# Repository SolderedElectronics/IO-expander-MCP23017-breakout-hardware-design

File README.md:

# IO expander MCP23017 breakout Hardware Design

## About the Product

|  |
| :----------------------------------------------------------: |
| [Buy IO expander MCP23017 breakout](https://www.solde.red/333007) |

Are you short on IO pins? Looking to increase the number of them? That’s what the GPIO Expander MCP23017 is for! It uses I2C communication to do so. With just two wires, 16 new fully configurable digital IO pins are added to a microcontroller.

Due to the jumpers on the board, the I2C address of a device can be changed. Thus, eight breakout boards can be connected to a microcontroller. All of the pins on the expander board have pull-out resistors that can be turned on and off.

---

## Repository Contents

This repository contains all design files for IO expander MCP23017 breakout, organized as follows:

- **`CAD` folder**: Contains KiCAD design files, including:
  - Schematics
  - PCB layout
  - Panel PCB layout
  - Source 3D files in Fusion360, if any
  - All files are sorted by version with a detailed change log.
- **`OUTPUTS` folder**: Includes all production-ready files, such as:
  - Bill of Materials (BOM) and interactive BOM (iBOM)
  - PDF versions of schematics
  - 3D `.step` file of the board
  - 3D-printable models
  - Gerber files for PCB manufacturing
  - Image of the pinout of the board
  - Product image
  - Compliance, legal and generic sales documents

Refer to the `Change Log` in the CAD folder for details about updates between versions.

---

## Learn More About the Product

Beyond the repository, explore the following resources:

### Soldered Verify

The **Soldered Verify** system ensures every board you purchase from Soldered is fully functional. It also provides access to exclusive test data for your product. To get started, find the unique Soldered Verify ID on your product's packaging and enter the ID on the [Soldered Verify page](https://soldered.com/verify/) to access test results and additional product details.

### Soldered Community

Soldered Community is your go-to place for technical support. Our engineers track and answer all questions posted there, and it’s a great space for the maker community. Get answers to your questions and solutions for your challenges at [Soldered Community](https://soldered.com/community).

### solde.red

solde.red is an ultimate URL shortener and information hub. Access it by typing solde.red/ followed by your product SKU, e.g., [solde.red/333000](https://solde.red/333000), to find getting-started guides, datasheets, open-source hardware and software files, certifications, images, pinouts, and more. Read more about the shortener [here](https://solde.red/info/).

---

## Contributing

Contributions are welcome! Here’s how you can get involved:

- Submit pull requests to enhance the design or fix issues.
- Report bugs or problems by opening an issue.

We encourage community collaboration to make this product even better.

---

## About Soldered

[Soldered for Makers](https://soldered.com) specializes in designing and manufacturing electronic products tailored for enthusiasts, ranging from hobbyists to professionals. Our portfolio includes electronic boards, sensors, and actuators that are widely utilized in fields such as microelectronics, mechatronics, robotics, programming, and IoT. Every product we offer is designed in-house and built upon open-source hardware and software platforms. Proudly certified and manufactured within the European Union, our catalog likely includes the product you need for your project.

We complement these products with comprehensive tutorials and manuals, product descriptions, schematics, programming codes, and project examples. Our round-the-clock [customer and technical support](https://soldered.com/community) is available for all our products, irrespective of the sales channel. Soldered’s success and services reflect our maker community’s unwavering [trust](https://www.trustpilot.com/review/soldered.com), for which we are deeply grateful. Join our community and create using Soldered products.

---

## License

All Soldered open-source hardware (OSH) is under The TAPR Open Hardware License. Read more in the LICENSE file located in this repository.

**Disclaimer:**

No warranty - all designs in this repository are distributed in the hope that they will be useful, but without any warranty. They are provided "AS IS", therefore without warranty of any kind, either expressed or implied. The entire quality and performance of what you do with the contents of this repository are your responsibility. In no event Soldered Electronics will be liable for your damages, or losses, including any general, special, incidental, or consequential damage arising out of the use or inability to use the contents of this repository. 

---

## Have fun!

Thank you for your support from your fellow makers at Soldered Electronics.

Happy Making!

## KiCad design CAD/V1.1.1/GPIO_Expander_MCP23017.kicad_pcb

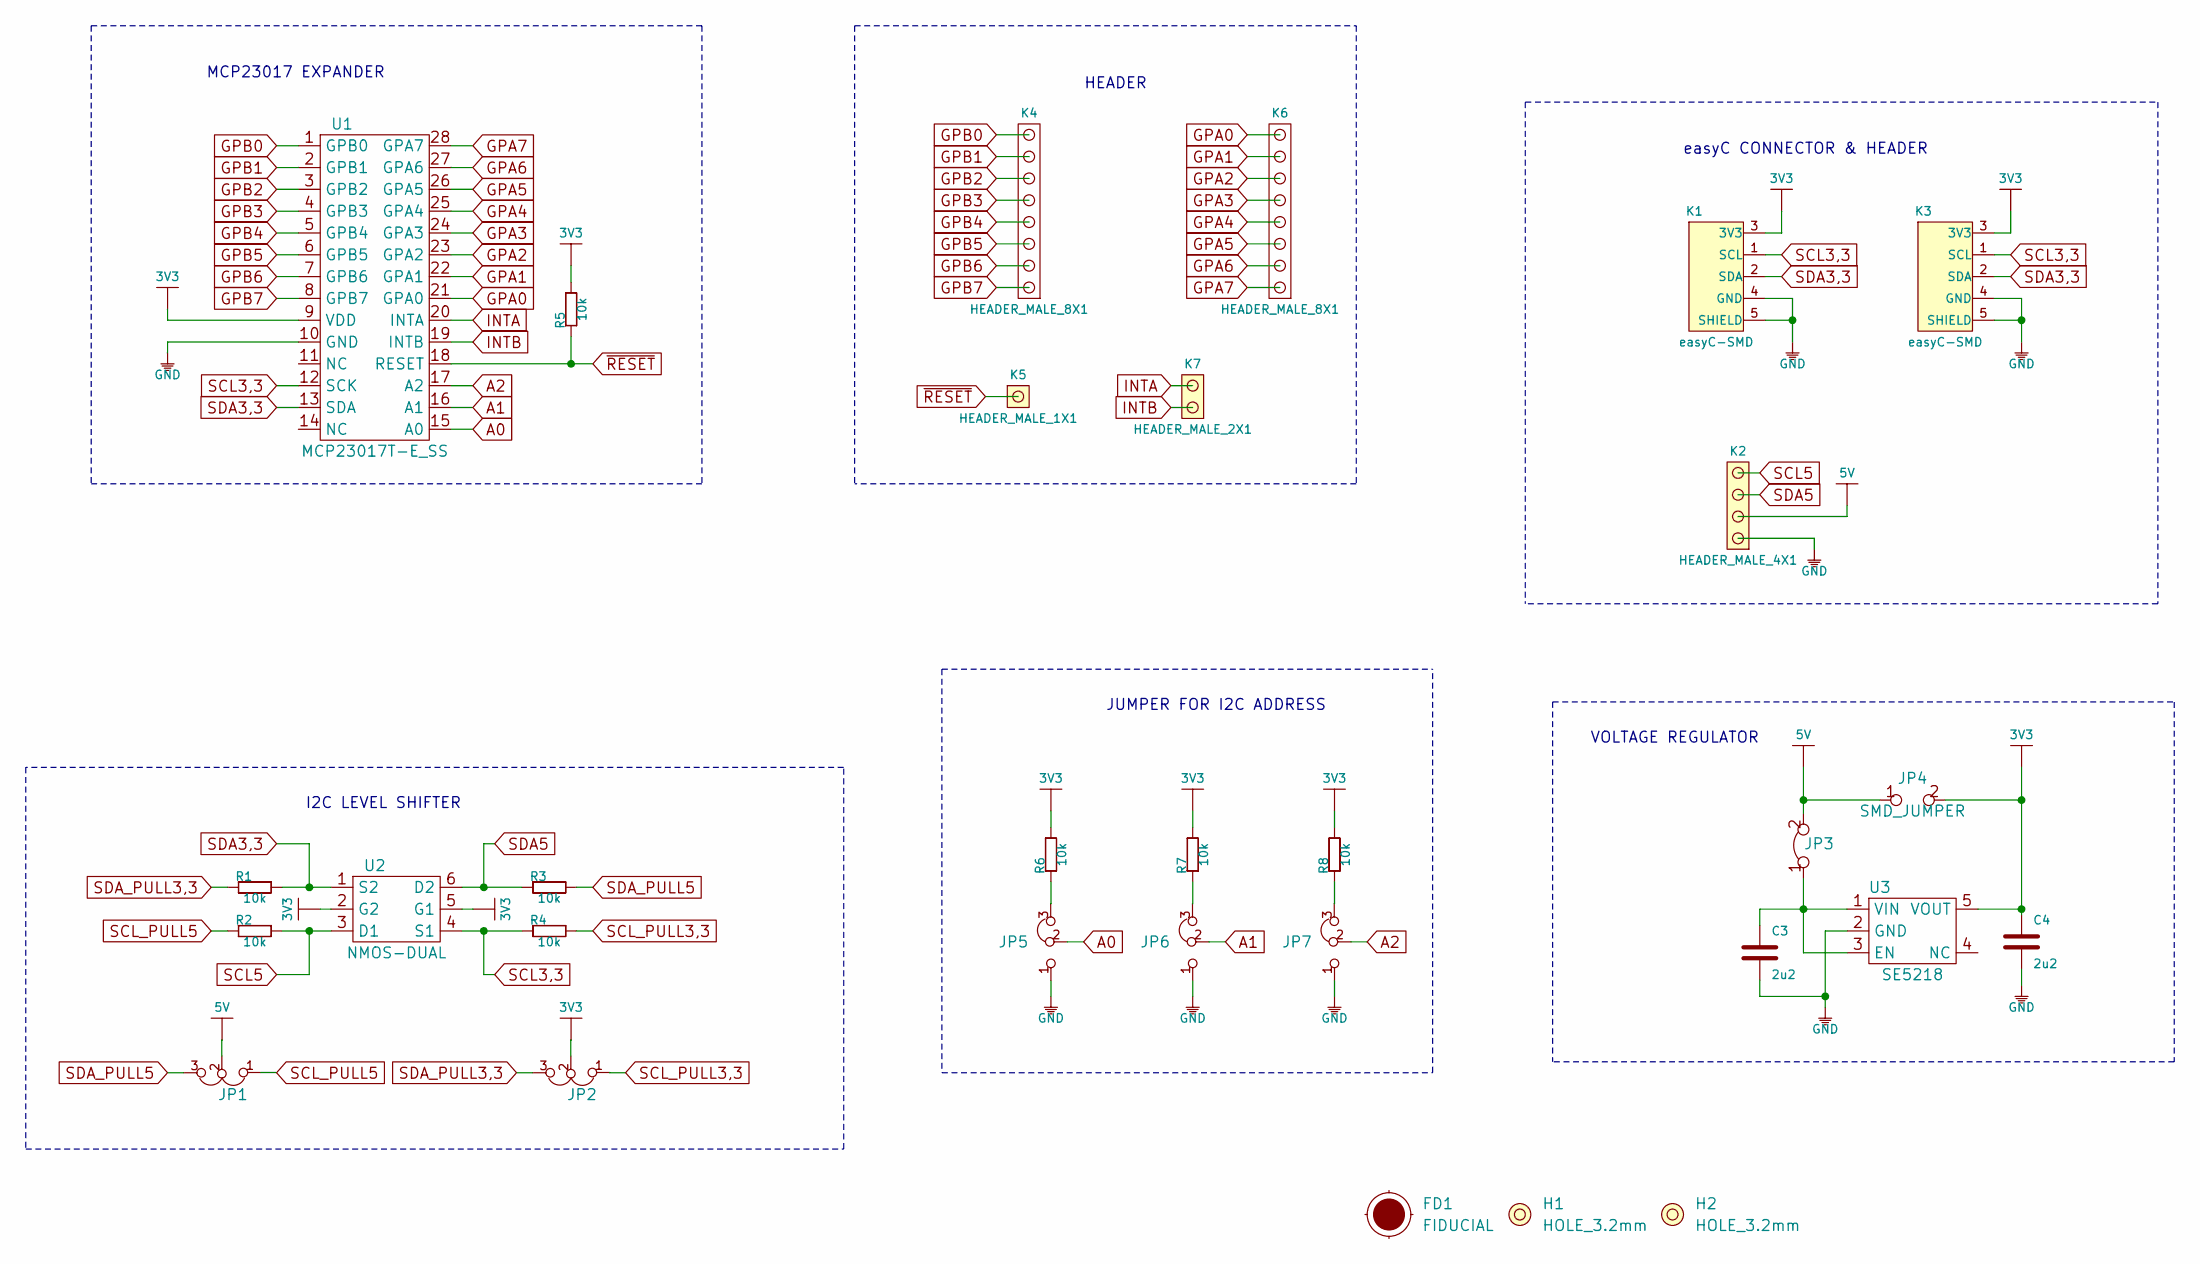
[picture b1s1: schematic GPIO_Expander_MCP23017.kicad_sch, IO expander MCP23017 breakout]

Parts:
C3, C4: 2u2; 0603C
FD1: FIDUCIAL; FIDUCIAL_23
H1, H2: HOLE_3.2mm
JP1, JP2: SMD_JUMPER_3_PAD_TRACE
JP3: SMD-JUMPER-CONNECTED_TRACE_SLODERMASK
JP4: SMD_JUMPER
JP5, JP6, JP7: SMD_JUMPER_3_PAD_CONNECTED_RIGHT
K1, K3: easyC-SMD; easyC-connector
K2: HEADER_MALE_4X1
K4, K6: HEADER_MALE_8X1
K5: HEADER_MALE_1X1
K7: HEADER_MALE_2X1
R1, R2, R3, R4, R5, R6, R7, R8: 10k; 0603R
U1: MCP23017T-E_SS; MCP23017
U2: NMOS-DUAL; SOT-363
U3: SE5218; SOT-23-5

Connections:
3V3: C4.2, JP2.2, JP4.2, K1.3 (3V3), K3.3 (3V3), R5.2, R6.2, R7.2, R8.2, U1.9 (VDD), U2.2 (G2), U2.5 (G1), U3.5 (VOUT)
5V: JP1.2, JP3.2, JP4.1, K2.2
A0: JP5.2, U1.15 (A0)
A1: JP6.2, U1.16 (A1)
A2: JP7.2, U1.17 (A2)
GND: C3.1, C4.1, JP5.1, JP6.1, JP7.1, K1.4 (GND), K1.5 (SHIELD), K2.1, K3.4 (GND), K3.5 (SHIELD), U1.10 (GND), U3.2 (GND)
GPA0: K6.8, U1.21 (GPA0)
GPA1: K6.7, U1.22 (GPA1)
GPA2: K6.6, U1.23 (GPA2)
GPA3: K6.5, U1.24 (GPA3)
GPA4: K6.4, U1.25 (GPA4)
GPA5: K6.3, U1.26 (GPA5)
GPA6: K6.2, U1.27 (GPA6)
GPA7: K6.1, U1.28 (GPA7)
GPB0: K4.8, U1.1 (GPB0)
GPB1: K4.7, U1.2 (GPB1)
GPB2: K4.6, U1.3 (GPB2)
GPB3: K4.5, U1.4 (GPB3)
GPB4: K4.4, U1.5 (GPB4)
GPB5: K4.3, U1.6 (GPB5)
GPB6: K4.2, U1.7 (GPB6)
GPB7: K4.1, U1.8 (GPB7)
INTA: K7.2, U1.20 (INTA)
INTB: K7.1, U1.19 (INTB)
unnamed: C3.2, JP3.1, U3.1 (VIN), U3.3 (EN)
unnamed: JP5.3, R6.1
unnamed: JP6.3, R7.1
unnamed: JP7.3, R8.1
SCL3,3: K1.1 (SCL), K3.1 (SCL), R4.1, U1.12 (SCK), U2.4 (S1)
SCL5: K2.4, R2.2, U2.3 (D1)
SCL_PULL3,3: JP2.1, R4.2
SCL_PULL5: JP1.1, R2.1
SDA3,3: K1.2 (SDA), K3.2 (SDA), R1.2, U1.13 (SDA), U2.1 (S2)
SDA5: K2.3, R3.1, U2.6 (D2)
SDA_PULL3,3: JP2.3, R1.1
SDA_PULL5: JP1.3, R3.2
~RESET: K5.1, R5.1, U1.18 (RESET)

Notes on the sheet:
I2C LEVEL SHIFTER
MCP23017 EXPANDER
VOLTAGE REGULATOR
easyC CONNECTOR & HEADER
JUMPER FOR I2C ADDRESS
HEADER

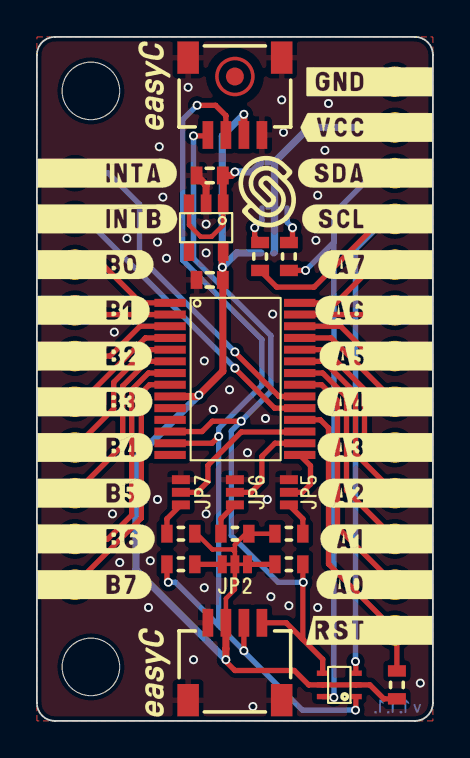
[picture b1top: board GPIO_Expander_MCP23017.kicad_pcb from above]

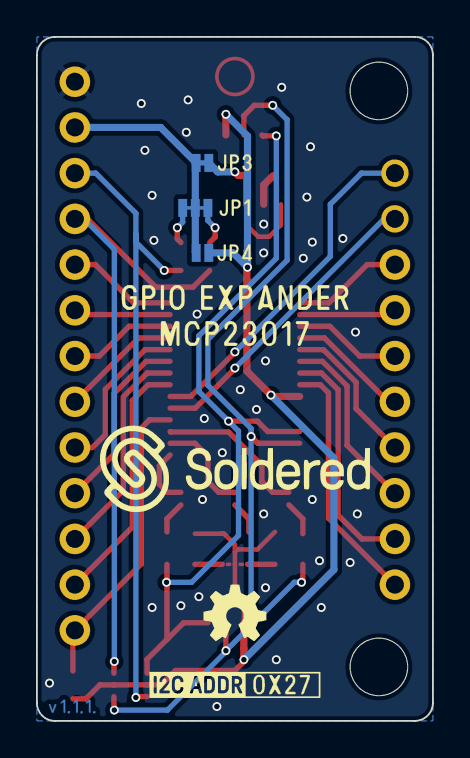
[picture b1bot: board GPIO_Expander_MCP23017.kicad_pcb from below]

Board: 2 copper layers, 22.0 x 38.0 mm, 30 parts (8 on the bottom side), 37 nets.

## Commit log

2022-08-06 Updating open source files.
